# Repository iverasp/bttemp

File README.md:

## BTTemp

A bluetooth device that broadcasts the temperature of a thermocouple

### Parts

- Attiny45
- MAX31855
- HC-05
- LM3940
- K-type thermocouple
- Misc. capacitors

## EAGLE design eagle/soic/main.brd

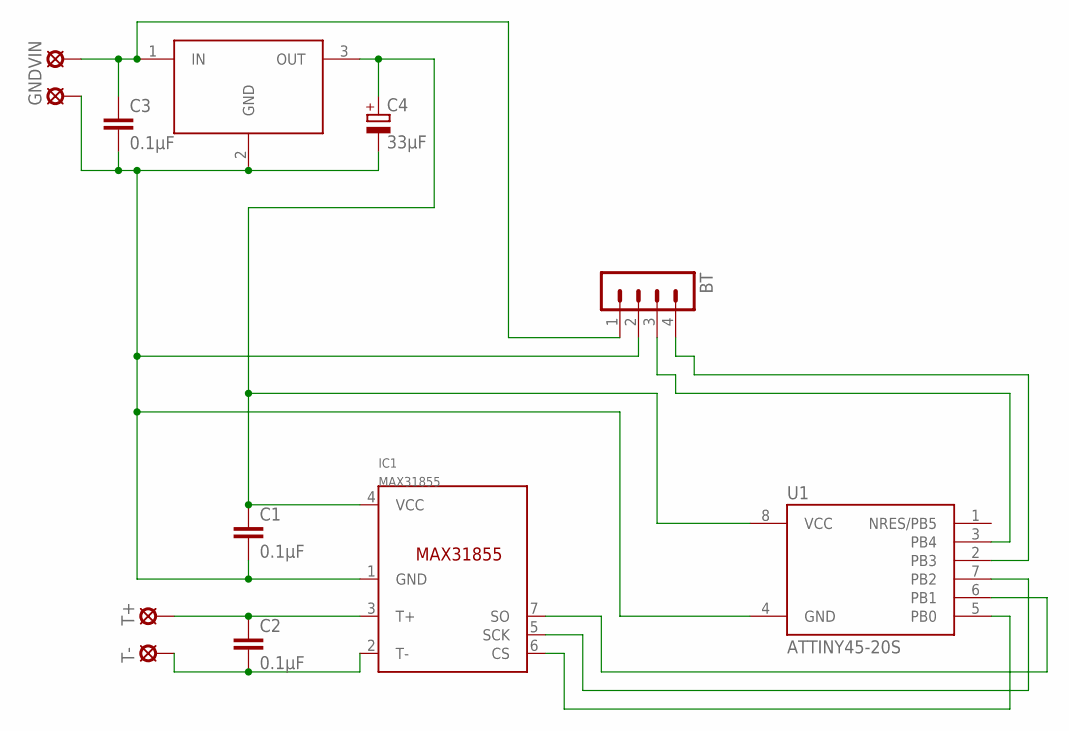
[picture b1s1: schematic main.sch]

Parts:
BT: MA04-1
C1, C2, C3: 0.1μF; C1206
C4: 33μF; E1,8-4
GND: LSP13
IC1: MAX31855; SOIC8
IC2: LM3940IMP-3.3; SOT223
T+: LSP13
T-: LSP13
U1: ATTINY45-20S; SOIC8_EIAJ_208MIL
VIN: LSP13

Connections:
unnamed: IC1.5 (SCK), U1.7 (PB2)
unnamed: BT.2, C1.2, C3.2, C4.-, GND.MP, IC1.1 (GND), IC2.2 (GND), U1.4 (GND)
unnamed: C2.1, IC1.3 (T+), T+.MP
unnamed: C2.2, IC1.2 (T-), T-.MP
unnamed: IC1.6 (CS), U1.5 (PB0)
unnamed: IC1.7 (SO), U1.6 (PB1)
unnamed: C1.1, C4.+, IC1.4 (VCC), IC2.3 (OUT), U1.8 (VCC)
unnamed: BT.1, C3.1, IC2.1 (IN), VIN.MP
unnamed: BT.3, U1.3 (PB4)
unnamed: BT.4, U1.2 (PB3)

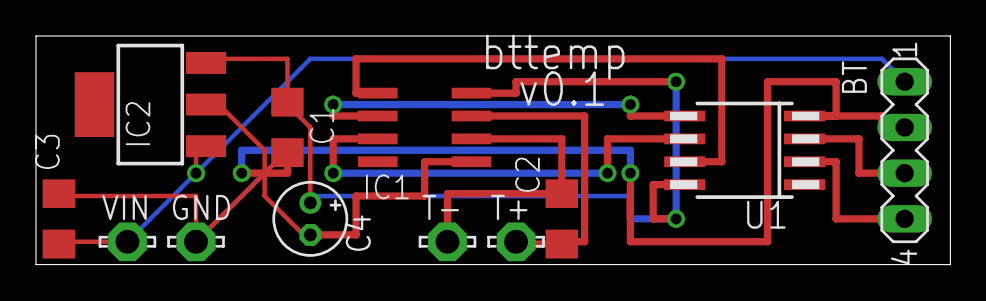
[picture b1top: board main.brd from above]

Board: 2 copper layers, 50.8 x 12.7 mm, 12 parts (0 on the bottom side), 10 nets.

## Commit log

2014-03-28 pcb with attiny in DIP package
2014-03-28 added readme
2014-03-28 added gitignore
2014-03-28 created folder
2014-03-30 initial code for arduino mcu
2014-03-31 pcb with all ic's in soic package
2014-04-02 initial android code
2014-04-03 updated gitignore
